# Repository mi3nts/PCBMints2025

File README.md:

# PCBMints2025
Contains PCB designs for MINTS Projects

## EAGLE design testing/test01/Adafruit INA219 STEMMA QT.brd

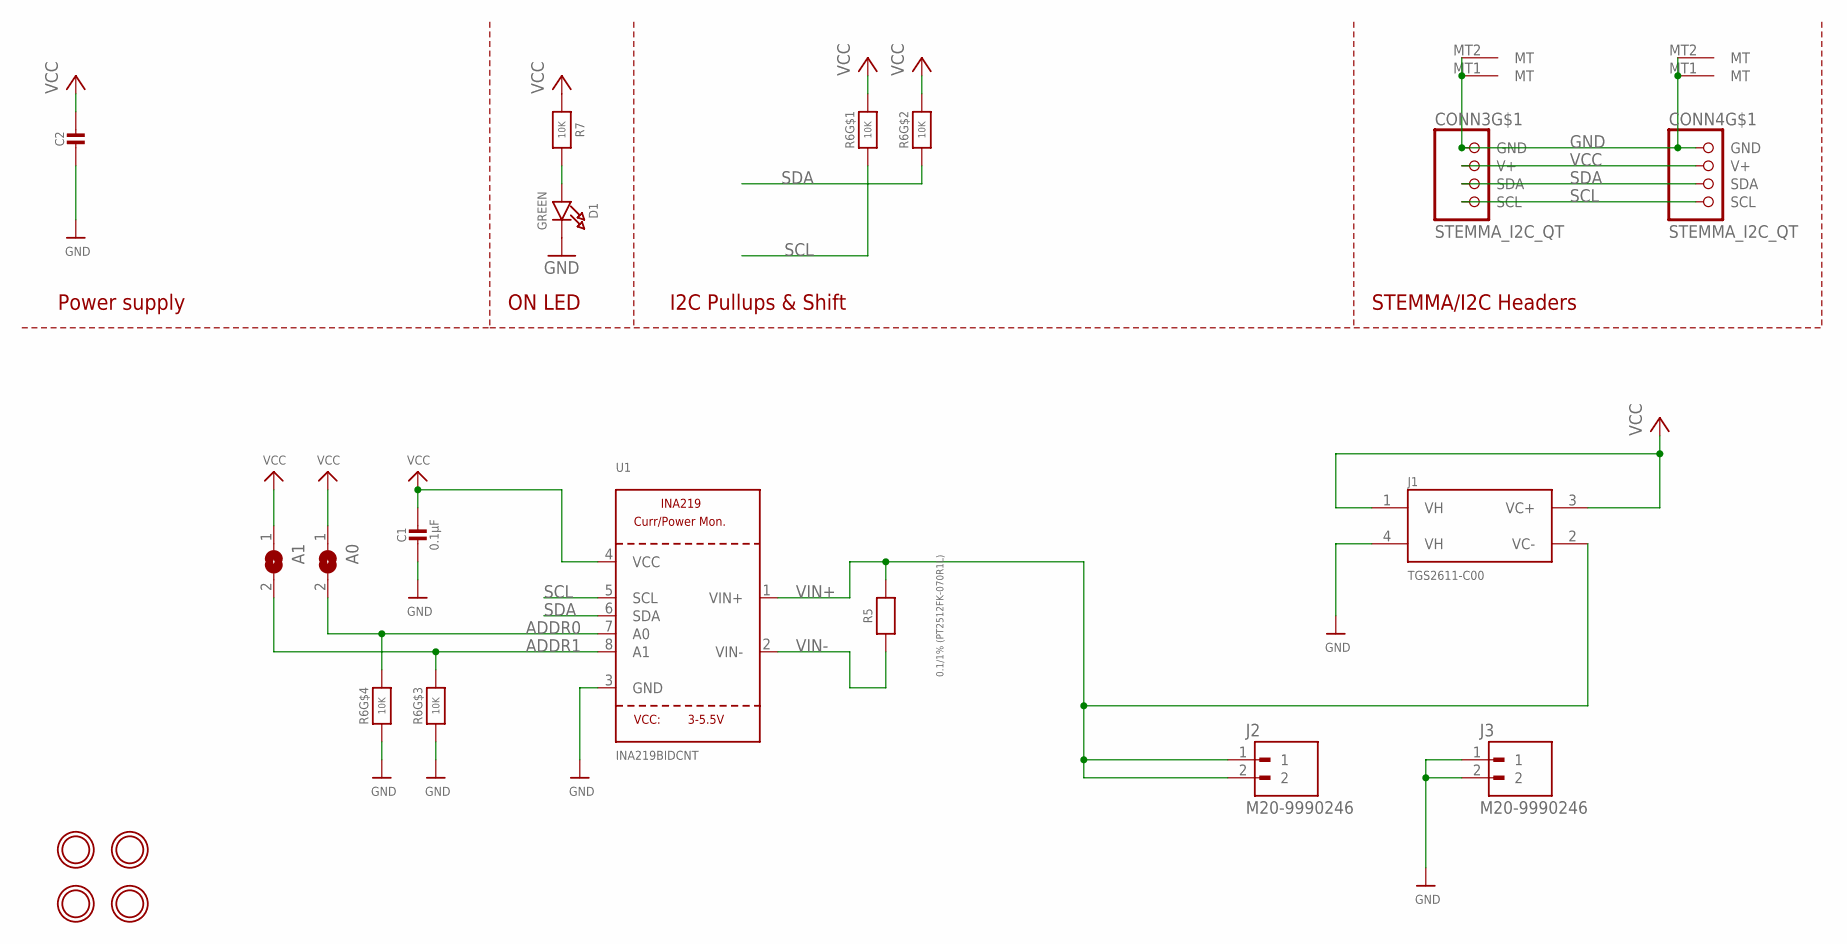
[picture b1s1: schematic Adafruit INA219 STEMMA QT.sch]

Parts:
A0, A1: SOLDERJUMPERREFLOW_NOPASTE; SOLDERJUMPER_REFLOW_NOPASTE
C1: 0.1µF; 0603-NO
C2: 10uF; 0805-NO
CONN3, CONN4: STEMMA_I2C_QT; JST_SH4
D1: GREEN; CHIPLED_0603_NOOUTLINE
J1: TGS2611-C00; TO180P920X780-4P
J2, J3: M20-9990246; HARWIN_M20-9990246
R5: 0.1/1% (PT2512FK-070R1L); 2512
R6: 10K; RESPACK_4X0603
R7: 10K; 0603-NO
U1: INA219BIDCNT; SOT23-8
U$20, U$21, U$25, U$27: MOUNTINGHOLE2.5; MOUNTINGHOLE_2.5_PLATED

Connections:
ADDR0: A0.2, R6.5 (2), U1.7 (A0)
ADDR1: A1.2, R6.6 (2), U1.8 (A1)
GND: C1.2, C2.2, CONN3.1 (GND), CONN3.MT1 (MT), CONN3.MT2 (MT), CONN4.1 (GND), CONN4.MT1 (MT), CONN4.MT2 (MT), D1.C, J1.4 (VH), J3.1, J3.2, R6.3 (1), R6.4 (1), U1.3 (GND)
unnamed: D1.A, R7.2
SCL: CONN3.4 (SCL), CONN4.4 (SCL), R6.1, U1.5 (SCL)
SDA: CONN3.3 (SDA), CONN4.3 (SDA), R6.2 (1), U1.6 (SDA)
VCC: A0.1, A1.1, C1.1, C2.1, CONN3.2 (V+), CONN4.2 (V+), J1.1 (VH), J1.3 (VC+), R6.7 (2), R6.8 (2), R7.1, U1.4 (VCC)
VIN+: J1.2 (VC-), J2.1, J2.2, R5.2, U1.1 (VIN+)
VIN-: R5.1, U1.2 (VIN-)

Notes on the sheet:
I2C Pullups & Shift
STEMMA/I2C Headers
ON LED
Power supply

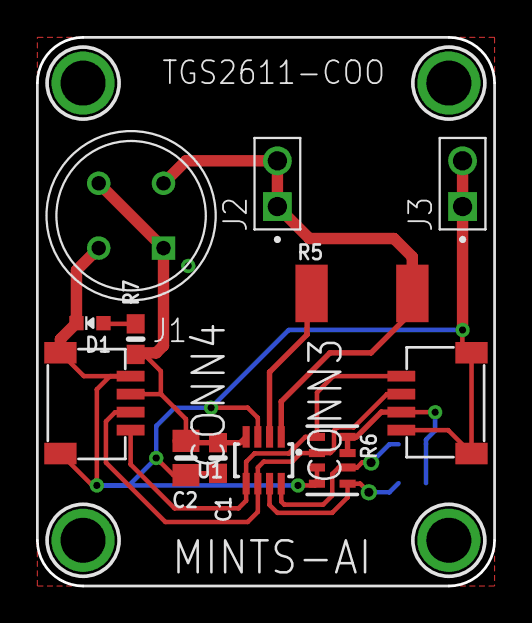
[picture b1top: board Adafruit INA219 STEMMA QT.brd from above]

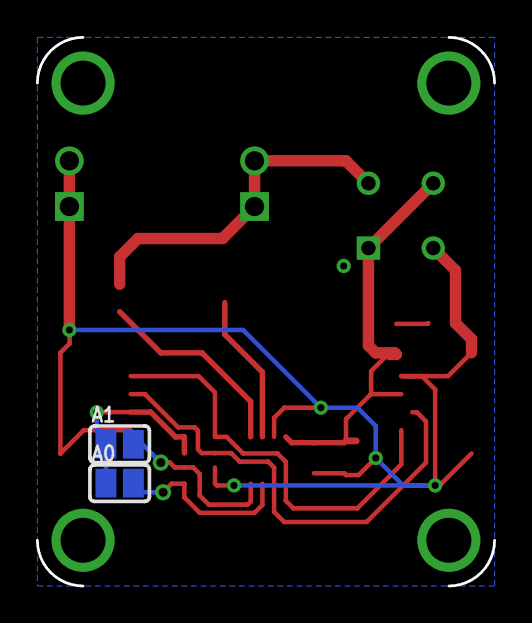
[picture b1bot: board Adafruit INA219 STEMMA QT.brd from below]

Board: 2 copper layers, 25.4 x 30.5 mm, 18 parts (2 on the bottom side), 9 nets.

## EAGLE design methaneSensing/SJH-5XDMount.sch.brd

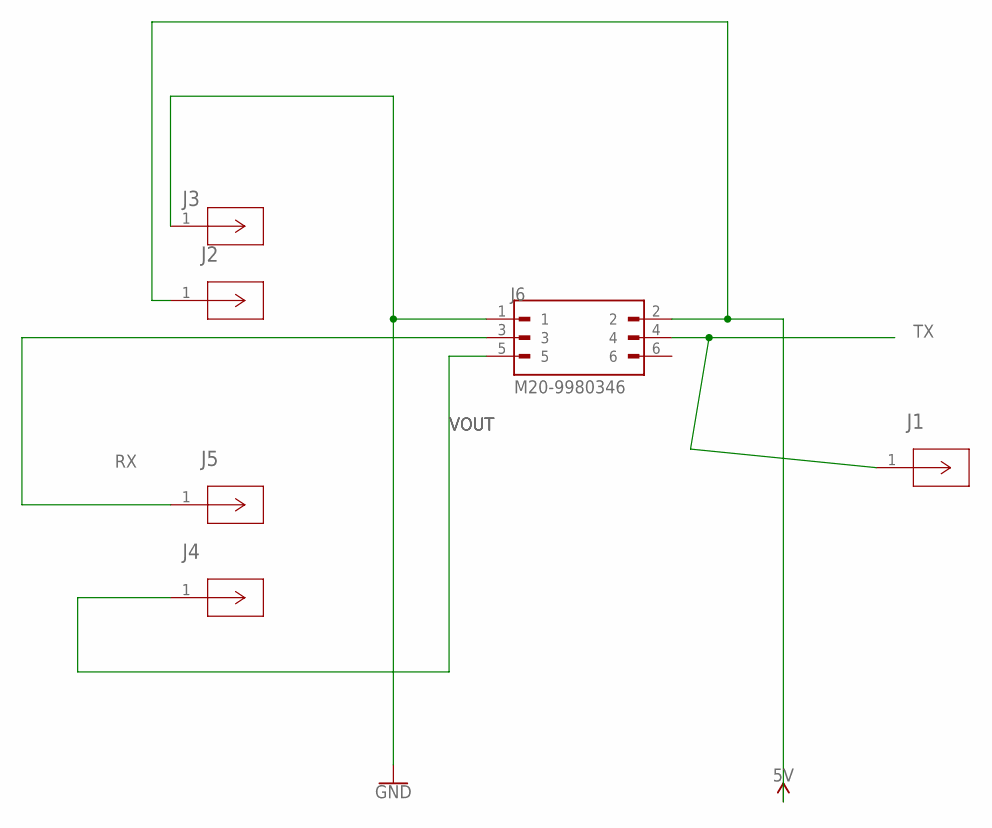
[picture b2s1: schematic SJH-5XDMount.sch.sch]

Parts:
J1, J2, J3, J4, J5: 450-3326-01-03-00; CONN_450-3326-01-XX-00_CBN
J6: M20-9980346; HARWIN_M20-9980346

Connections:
5V: J2.1, J6.2
GND: J3.1, J6.1
RX: J5.1, J6.3
TX: J1.1, J6.4
VOUT: J4.1, J6.5

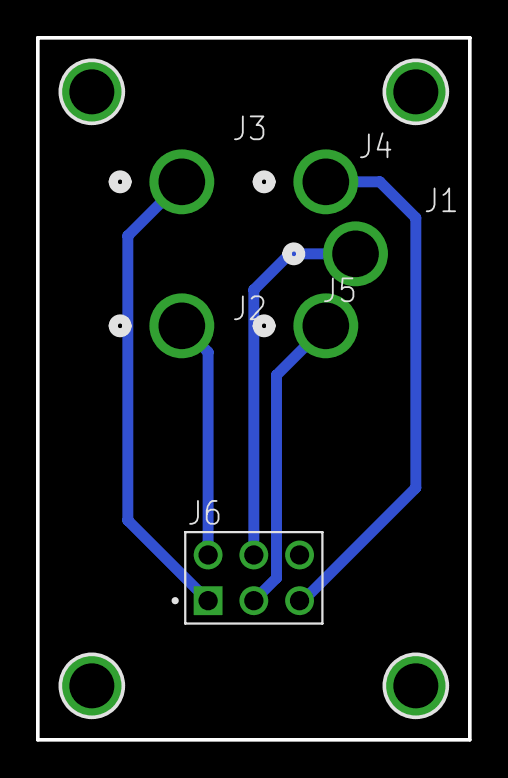
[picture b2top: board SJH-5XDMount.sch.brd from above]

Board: 2 copper layers, 24.0 x 39.0 mm, 10 parts (0 on the bottom side), 5 nets.

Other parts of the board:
U$1, U$2, U$3, U$4: MOUNTINGHOLE2.5; MOUNTINGHOLE_2.5_PLATED

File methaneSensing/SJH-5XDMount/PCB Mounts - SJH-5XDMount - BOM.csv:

,,,,,,,,,,,,,,,,
,,,,,,,,,,,,,,,,
Qty,Designator,Footprint,Comment,Description,,,,,,,,,,,,
5,"J1, J2, J3, J4, J5",450-3326-01-03-00,CONN_450-3326-01-XX-00_CBN,Cambion 450-3326-01-03-00,,,,,,,,,,,,
1,J6,M20-9980346,HARWIN_M20-9980346,HARWIN,,,,,,,,,,,,
4,"U$1, U$2, U$3, U$4",MOUNTINGHOLE2.5,MOUNTINGHOLE_2.5_PLATED,Mounting Hole,,,,,,,,,,,,
,,,,,,,,,,,,,,,,
,,,,,,,,,,,,,,,,
,,,,,,,,,,,,,,,,
,,,,,,,,,,,,,,,,
,,,,,,,,,,,,,,,,
,,,,,,,,,,,,,,,,
,,,,,,,,,,,,,,,,
,,,,,,,,,,,,,,,,
,,,,,,,,,,,,,,,,
,,,,,,,,,MAXIMUM_PACKAGE_HEIGHT,MFR_NAME,PARTREV,STANDARD,,,,
,,,,,,,,,,Cambion,,,,,,
,,,,,,,,,,,,Manufacturer Recommendations,,,,
,,,,,,,,,,,,,,,,
,,,,,,,,,,,,,,,,
,,,,,,,,,,,,,,,,
,,,,,,,,,,,,,,,,
,,,,,,,,,Description,COPYRIGHT,MANUFACTURER,MANUFACTURER_PART_NUMBER,MAXIMUM_PACKAGE_HEIGHT,MFR_NAME,PARTREV,STANDARD
,,,,,,,,,,Copyright (C) 2024 Ultra Librarian. All rights reserved.,,450-3326-01-03-00,,Cambion,,
,,,,,,,,,,,HARWIN,,,,,Manufacturer Recommendations
,,,,,,,,,Mounting Hole,,,,,,,

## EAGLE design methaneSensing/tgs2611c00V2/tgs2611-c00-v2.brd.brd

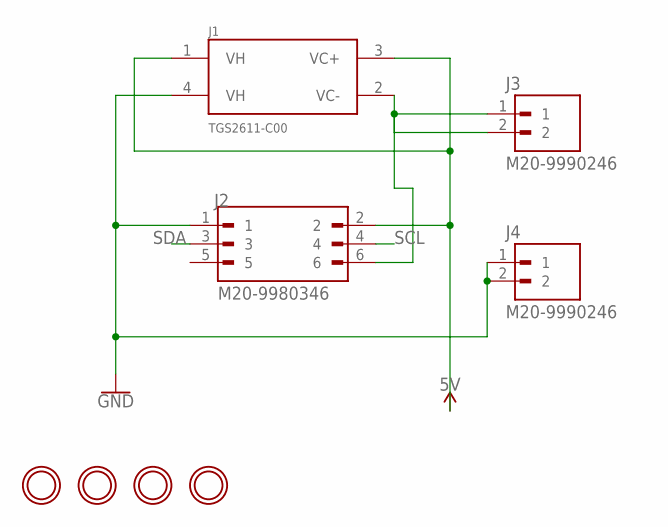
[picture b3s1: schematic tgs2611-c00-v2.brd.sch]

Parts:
J1: TGS2611-C00; TO180P920X780-4P
J2: M20-9980346; HARWIN_M20-9980346
J3, J4: M20-9990246; HARWIN_M20-9990246
U$1, U$2, U$3, U$4: MOUNTINGHOLE2.5; MOUNTINGHOLE_2.5_PLATED

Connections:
5V: J1.1 (VH), J1.3 (VC+), J2.2
GND: J1.4 (VH), J2.1, J4.1, J4.2
unnamed: J1.2 (VC-), J2.6, J3.1, J3.2
SCL: J2.4
SDA: J2.3

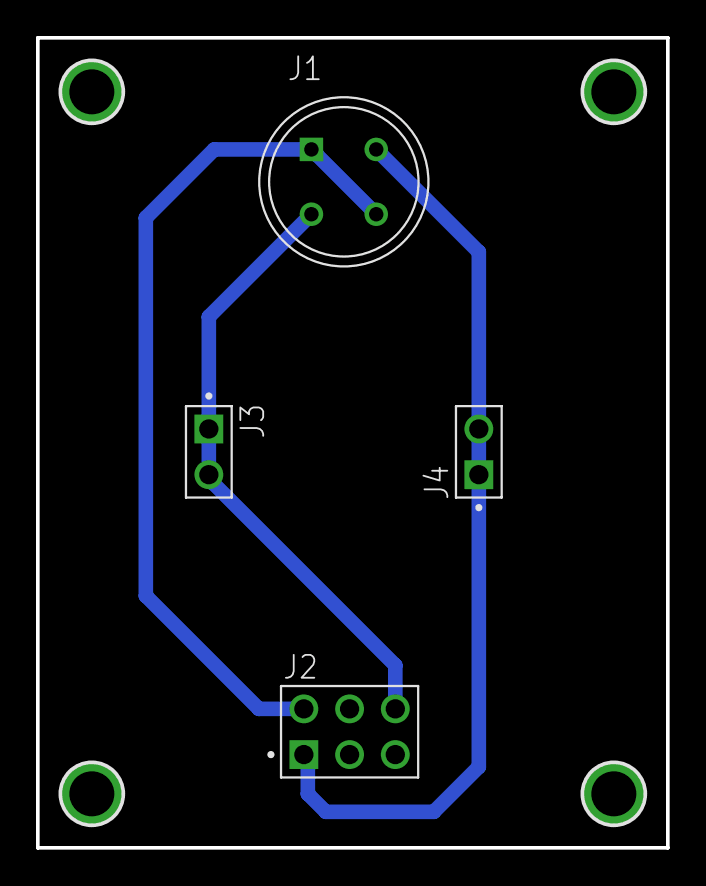
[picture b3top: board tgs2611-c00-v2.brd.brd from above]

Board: 2 copper layers, 35.0 x 45.0 mm, 8 parts (0 on the bottom side), 3 nets.

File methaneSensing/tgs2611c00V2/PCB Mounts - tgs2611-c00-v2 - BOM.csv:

Qty,Designator,Footprint,Comment,Description
1,J2,M20-9980346,M20-9980346,HARWIN_M20-9980346
2,"J3, J4",M20-9990246,M20-9990246,HARWIN_M20-9990246
4,"U$1, U$2, U$3, U$4",MOUNTINGHOLE2.5,MOUNTINGHOLE2.5,MOUNTINGHOLE_2.5_PLATED
1,J1,TGS2611-C00,TGS2611-C00,"TO180P920X780-4P - Methane, Natural Gas sensor"

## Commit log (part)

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2024-11-26 minor updates
2024-11-27 methane PCBs added
2025-09-03 Dream Added
2025-09-04 dream updates
2025-09-04 major updates
2025-09-23 PCB updates for dream
2025-10-23 added hat outline pcb
2025-10-30 update_hat
2025-10-30 update hat; PCB reset
2025-10-31 update hat
2025-11-06 added some to scale drawings for layout design
2026-01-01 Add files via upload
    Type C moved to be above the GPIO, new switch, subtle mounting hole, and border changes.
2026-01-02 reverted file structure to contain both v1 and v2
2026-01-09 fixed unconnected line
2026-01-09 Updated gerber
2026-01-12 Updated ibom
2026-02-24 created DreamLeo directory
2026-02-24 Add files via upload
    DreamLeo uploaded
2026-06-02 Add files via upload
    new update after various labeling and cleaning up,
2026-06-02 update silkscreen
2026-06-05 Add files via upload
    finishing touches on edge cut and errors
2026-06-11 Add files via upload
    methane sens flipped and clutter cleaned by gpio3 and 90s cleaned, copper zone added on f.cu and DRC ran and checked. spi logo moved. all the lose traces I could find I cut.
2026-06-11 partially fixed leo board
2026-06-11 restarted traces
2026-06-11 halfway done v3
2026-06-12 almost done; need to clean up bottom half maybe
2026-06-15 fixed issues; update schematic
2026-06-15 update structure
2026-06-18 final john update
2026-06-27 Final draft DREAM V3
2026-06-27 remove user file
2026-06-30 update nosilk model
2026-06-30 Final DreamV3
2026-06-30 Updated Throughhole

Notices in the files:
parts and their libraries:
microbuilder: This work is placed in the public domain, and may be freely used for commercial and non-commercial work with the following conditions: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
COPYRIGHT: Copyright (C) 2024 Ultra Librarian. All rights reserved.
